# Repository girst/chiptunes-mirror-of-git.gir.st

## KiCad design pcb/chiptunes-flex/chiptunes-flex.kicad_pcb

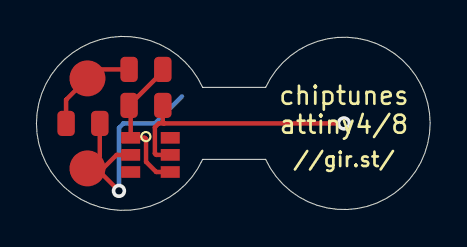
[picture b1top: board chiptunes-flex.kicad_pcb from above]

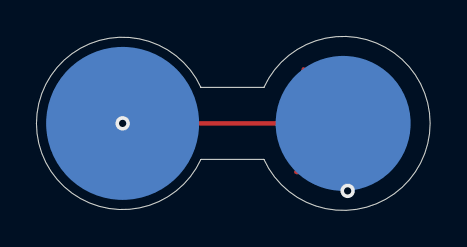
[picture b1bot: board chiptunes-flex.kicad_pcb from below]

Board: 2 copper layers, 21.9 x 9.7 mm, 8 parts (2 on the bottom side), 4 nets.

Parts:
C1: 100n; C_0805_2012Metric
R1: 100k; R_0805_2012Metric
R2: 200; R_0805_2012Metric
TP1: bat+; TestPoint_Pad_D2.0mm
TP2: bat-; TestPoint_Pad_D2.0mm
TP3: audio+; TestPoint_Pad_D2.0mm
TP4: audio-; TestPoint_Pad_D2.0mm
U1: ATtiny4-TS; SOT-23-6

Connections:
+3V0: R1.1, TP1.1, U1.5
GND: C1.2, TP2.1, TP4.1, U1.2
unnamed: C1.1, R2.1, TP3.1
unnamed: R1.2, R2.2, U1.1, U1.4

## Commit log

2018-11-12 new version
2018-11-13 new version
    WARN: breaks at ~ 70min, but who cares
2018-11-13 new version
    move `x` out of g(), so we can use it as tempvar in g()
2018-11-13 new version
    move `o` out of g() to get rid of variable shift
2018-11-13 new version
    can now get rid of `o` completely, saving 1 register
2018-11-13 new version
    use `_` as tmpregister consistently; use x as Xhi
2018-11-13 new version
    check which registers are first used by MOV, which rely on being cleared
2018-11-13 new version
    var to register association (not final, but close)
2018-11-18 new version
    NOTE: `t` and `x` registers swapped, otherwise we would overwrite Xlo
2018-11-18 new version
    bring cycle count down from 425 to 409
2018-12-11 new version
    using this we can save a few more cycles (code size not yet compared).
    working principle:
    we can distinguish which number to multiply by with the lower nibble
    only. to have maximum overlap, use a decision tree to select where to
    go. the upper nibble is then just a straight path (there is not much
    to deduplicate).
2018-12-11 import Makefile
2018-12-11 preparing for C -> ASM
2018-12-11 transcribe fakeasm into realasm (I)
2018-12-11 transcribe fakeasm into realasm (II)
2018-12-11 transcribe fakeasm into realasm (III)
2018-12-11 transcribe fakeasm into realasm (IV)
2018-12-11 initialisation code, interrupt vector table
    it werks! (it's completely out of tune and too fast, but audio is coming
    out of the chip. program at 5v, then play at 3v3. chip can't handle the
    stereo amp, but headphones work)
2018-12-11 add debug pin, remove 2 unnecessary instructions
2018-12-11 refactor mul .macros
2018-12-11 optimize mul_8c / mul_84
2018-12-11 swap registers for `t` and `_`
    LDing to Xhi or Xlo is undefined, so we had to move `t` somewhere else
    and then back. swapping these registers globally solves this.
    also rename 'data' to 'notes' to be more expressive
2018-12-11 remove dedicated zero register (saves 4 bytes of progmem)
2018-12-13 fix bug: a2 (as tmp) was not cleared after use
2018-12-14 fix Ml register, clear interrupt before RETI
2018-12-18 fix jitter
    yeah...don't rjmp into interrupt instead of main loop m(
2018-12-21 calibrate oscillator
    just measure frequency of PORTB2 and fiddle with the number until it's
    close enough. don't forget to hold your tongue at the right angle!
2018-12-21 it werks!
    putting the notes into .text instead of .data was orignially inteded to
    "look better" in avr-size, but actually fixed the
    wrong-notes-played-problem!?
2018-12-21 conserve 6 bytes of progmem
    replace NOPs in intr.vector with useful instructions
2018-12-21 cleanup some TODOs, #defines
2018-12-21 cleanup some TODOs, #defines
    also: hide PORTB2 behind -DDEBUG to save 4 bytes :D
2018-12-24 deduplicate code for attiny4
    > avr-size -C --mcu=attiny4 foo.elf
    > AVR Memory Usage
    > ----------------
    > Device: attiny4
    >
    > Program: 446 bytes (87.1% Full)
2020-03-01 fix melody for voices 3 and 4
    15 months later, I took another look at why the music was off for
    channels 3 and 4 and pretty fast noticed that it affects only the voices
    using the mod3 subroutine. Executing mod3 with simavr[1] showed that the
    compare-branch step is broken. Switching BRPL for the correct BRCS fixed
    the problem.
    [1]: in the hackiest way imaginable:
2020-03-01 s/BRPL/BRCS/
2020-03-02 add note about decision tree multiplication
2020-03-02 optimize multiplication for space
    AVR Memory Usage
    ----------------
    Device: attiny4
    Program: 474 bytes (92.6% Full)
    (.text + .data + .bootloader)
    Data: 0 bytes (0.0% Full)
2020-03-07 first ideas regarding automatic power-off after 1 loop of playback
2020-03-07 first test of pcint0 implementation
    note: does not work, since nested interrupts are disabled by default,
    and we are not calling SEI before SLEEP. this makes the mcu never wake
    up again
2020-03-07 second test pcint0 implementation
2020-03-09 3rd iteration (still not working)
2020-03-09 remove i3
    since we are now stopping after each iteration, it makes no sense to go
    beyond 7864320 samples.
2020-07-16 cleanup; switch to INT0
    working with external pullup and pb0+pb2 shorted
2020-07-16 clean up registers
2020-07-16 cleanup a bit
2020-07-25 flex PCB, version 1
    as ordered from oshpark
2020-07-27 pcb: add low pass filter
2020-09-28 use BRMI instead of -CS
    since we only compare small positive integers, it doesn't matter, but
    BRCS/BRLO is unsigned comparison while BRMI is signed, what makes more
    sense.
2020-10-03 check in assembly notes
